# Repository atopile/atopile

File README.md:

# atopile

Design circuit boards with code.

**[Use atopile at atopile.io](https://atopile.io)**

The open-source code in this repository is licensed under [MIT](LICENSE).

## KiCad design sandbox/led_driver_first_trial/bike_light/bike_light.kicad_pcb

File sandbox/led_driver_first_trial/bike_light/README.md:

To add lib components: https://pypi.org/project/easyeda2kicad/

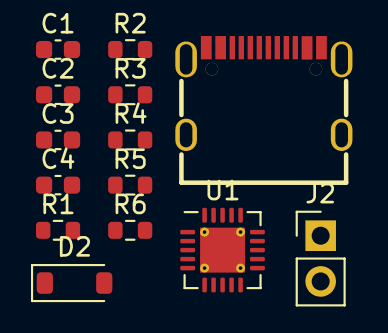
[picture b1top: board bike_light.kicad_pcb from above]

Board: 2 copper layers, 14 parts (0 on the bottom side), 14 nets, no tracks yet.

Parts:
C1: 3.3uF; C_0603_1608Metric
C2: 10uF; C_0603_1608Metric
C3: 33nF; C_0603_1608Metric
C4: 10nF; C_0603_1608Metric
D2: D_SOD-123
J1: USB-C-SMD_KH-TYPE-C-16P
J2: PinHeader_1x02_P2.54mm_Vertical
R1: 6.81k; R_0603_1608Metric
R2: 0.33R; R_0603_1608Metric
R3: 2.4k; R_0603_1608Metric
R4: 100k; R_0603_1608Metric
R5: 1M; R_0603_1608Metric
R6: 75k; R_0603_1608Metric
U1: QFN-20-1EP_4x4mm_P0.5mm_EP2.5x2.5mm_ThermalVias

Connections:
5: R2.2, U1.14
7: C2.1, D2.2, R2.1, R5.1, U1.13
8: J2.1, R4.1
10: R1.1, U1.4
11: C3.1, U1.6
13: R5.2, R6.1, U1.8
14: U1.9, U1.10
15: D2.1, U1.18
27: C4.1, R3.2
34: J1.A6, J1.B6
35: J1.A7, J1.B7
36: J1.A5, J1.B5
37: J1.A8, J1.B8
41: J1.A4, J1.A9, J1.B4, J1.B9

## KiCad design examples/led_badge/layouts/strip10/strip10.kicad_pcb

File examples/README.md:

# Examples

To run examples install faebryk either via pypi or locally with `pip install -e .`
Then you can run them with `python3 examples/<your example>`.

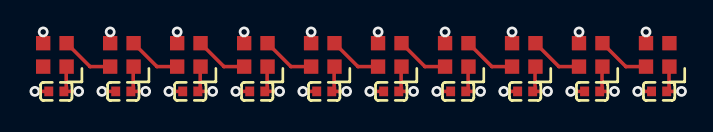
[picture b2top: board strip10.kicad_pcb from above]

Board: 2 copper layers, 20 parts (0 on the bottom side), 11 nets.

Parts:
C1, C2, C3, C4, C5, C6, C7, C8, C9, C10: 100nF; C0402
LED1, LED2, LED3, LED4, LED5, LED6, LED7, LED8, LED9, LED10: LED-SMD_4P-L2.0-W2.0-BR

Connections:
hv: C1.1, C2.1, C3.1, C4.1, C5.1, C6.1, C7.1, C8.1, C9.1, C10.1, LED1.1, LED2.1, LED3.1, LED4.1, LED5.1, LED6.1, LED7.1, LED8.1, LED9.1, LED10.1
leds[1]-data_in-DIN: LED1.2, LED2.4
leds[2]-data_in-DIN: LED2.2, LED3.4
leds[3]-data_in-DIN: LED3.2, LED4.4
leds[4]-data_in-DIN: LED4.2, LED5.4
leds[5]-data_in-DIN: LED5.2, LED6.4
leds[6]-data_in-DIN: LED6.2, LED7.4
leds[7]-data_in-DIN: LED7.2, LED8.4
leds[8]-data_in-DIN: LED8.2, LED9.4
leds[9]-data_in-DIN: LED9.2, LED10.4
lv: C1.2, C2.2, C3.2, C4.2, C5.2, C6.2, C7.2, C8.2, C9.2, C10.2, LED1.3, LED2.3, LED3.3, LED4.3, LED5.3, LED6.3, LED7.3, LED8.3, LED9.3, LED10.3

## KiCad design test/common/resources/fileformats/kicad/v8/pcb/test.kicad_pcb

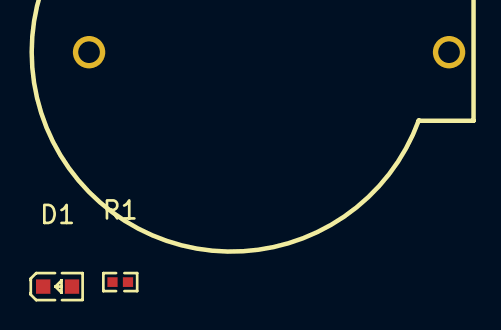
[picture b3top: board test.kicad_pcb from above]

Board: 2 copper layers, 3 parts (0 on the bottom side), 3 nets, no tracks yet.

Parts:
B1: ButtonCell; BAT-TH_BS-02-A1AJ010
D1: LED; LED0603-RD-YELLOW
R1: 40.2Ω; R0402

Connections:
B1-1-R1-2: B1.1, R1.2
B1-2-D1-2: B1.2, D1.2
D1-1-R1-1: D1.1, R1.1

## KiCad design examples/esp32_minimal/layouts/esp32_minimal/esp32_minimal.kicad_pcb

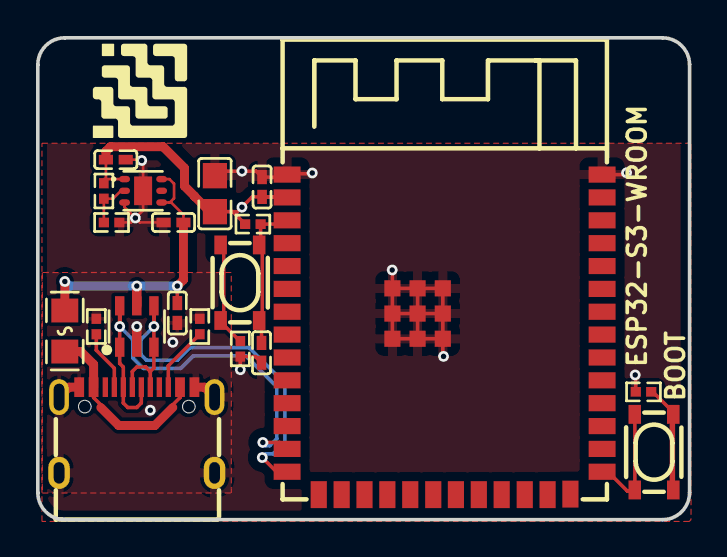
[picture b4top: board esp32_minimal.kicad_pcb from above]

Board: 2 copper layers, 36.2 x 26.8 mm, 20 parts (0 on the bottom side), 13 nets.

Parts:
C1, C2, C10: 1µF ±10% 25V X5R; C0402
C3, C8: 100nF ±10% 16V X7R; C0402
C9: 22µF ±20% 6.3V X5R; C0805
D1: SOT-23-6_L2.9-W1.6-P0.95-LS2.8-BL
F1: F0805
R1, R3: 10kΩ ±1% 62.5mW; R0402
R2, R4: 100Ω ±1% 62.5mW; R0402
R5: 47kΩ ±1% 62.5mW; R0402
R6, R7: 5.1kΩ ±1% 62.5mW; R0402
SW1, SW2: KEY-SMD_4P-L4.2-W3.2-P2.20-LS4.6
U2: WIRELM-SMD_ESP32-S3-WROOM-1
U3: WSON-6_L2.0-W2.0-P0.65-TL-EP
USB1: USB-C-SMD_TYPE-C-6PIN-2MD-073

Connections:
GND: C1.2, C2.2, C3.2, C8.2, C9.2, C10.2, D1.2, R1.2, R2.2, R4.2, R6.2, R7.2, U2.1, U2.40, U2.41, U3.3, U3.7, USB1.1, USB1.12, USB1.13, USB1.14, USB1.15, USB1.16
USB_D_N: D1.1, D1.6, U2.13, USB1.5, USB1.7
USB_D_P: D1.3, D1.4, U2.14, USB1.6, USB1.8
VDIV_OUTPUT: R1.1, R5.2, U3.2
button-input-input-0: R2.1, SW1.1, SW1.2
button-input-input-1: R4.1, SW2.1, SW2.2
cc[0]-line: R6.1, USB1.4
cc[1]-line: R7.1, USB1.10
gpios[0]-output: SW1.3, SW1.4, U2.27
output-output: C10.1, R3.1, SW2.3, SW2.4, U2.3
power-VCC: C2.1, C8.1, C9.1, R3.2, R5.1, U2.2, U3.1
power_in-VCC: C1.1, C3.1, D1.5, F1.2, U3.4, U3.6
power_vbus-VCC: F1.1, USB1.2, USB1.11

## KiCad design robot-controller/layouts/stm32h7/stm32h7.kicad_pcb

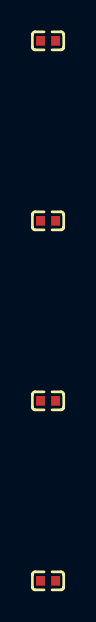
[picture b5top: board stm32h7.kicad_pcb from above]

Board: 2 copper layers, 4 parts (0 on the bottom side), 2 nets, no tracks yet.

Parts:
C1, C2, C3, C4: 0F; C0402

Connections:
hv: C1.1, C2.1, C3.1, C4.1
lv: C1.2, C2.2, C3.2, C4.2

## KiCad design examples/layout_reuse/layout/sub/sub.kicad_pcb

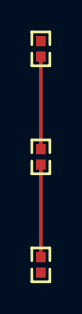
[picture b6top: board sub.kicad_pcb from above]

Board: 2 copper layers, 3 parts (0 on the bottom side), 2 nets.

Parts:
R1, R2, R3: 1kΩ; R0402

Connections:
unnamed[0]-1: R1.2, R2.1
unnamed[0]-2: R2.2, R3.1

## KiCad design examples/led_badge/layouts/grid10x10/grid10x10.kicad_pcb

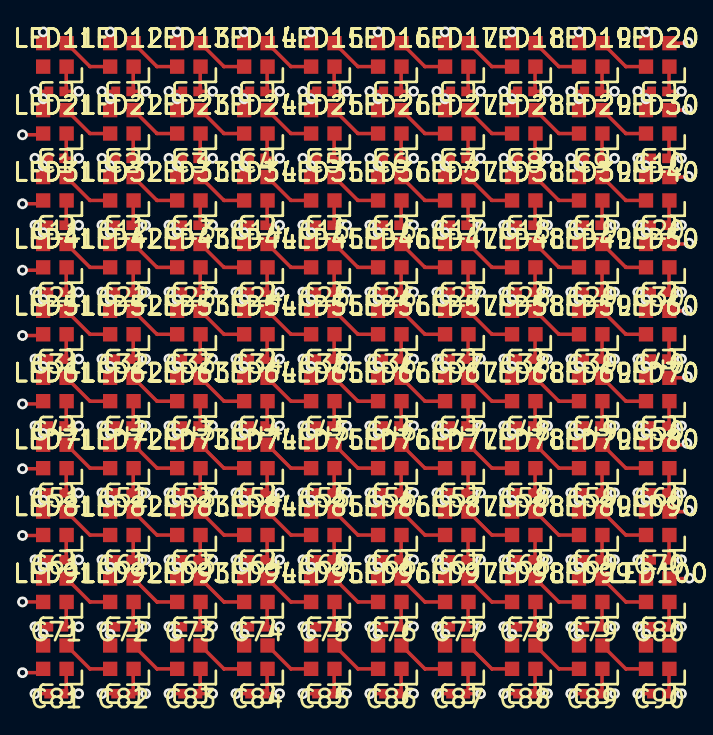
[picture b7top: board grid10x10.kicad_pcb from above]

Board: 4 copper layers, 200 parts (0 on the bottom side), 101 nets.

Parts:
C1, C2, C3, C4, C5, C6, C7, C8, C9, C10, C11, C12, C13, C14, C15, C16, C17, C18, C19, C20, C21, C22, C23, C24, C25, C26, C27, C28, C29, C30, C31, C32, C33, C34, C35, C36, C37, C38, C39, C40, C41, C42, C43, C44, C45, C46, C47, C48, C49, C50, C51, C52, C53, C54, C55, C56, C57, C58, C59, C60, C61, C62, C63, C64, C65, C66, C67, C68, C69, C70, C71, C72, C73, C74, C75, C76, C77, C78, C79, C80, C81, C82, C83, C84, C85, C86, C87, C88, C89, C90, C91, C92, C93, C94, C95, C96, C97, C98, C99, C100: 100nF; C0402
LED1, LED2, LED3, LED4, LED5, LED6, LED7, LED8, LED9, LED10, LED11, LED12, LED13, LED14, LED15, LED16, LED17, LED18, LED19, LED20, LED21, LED22, LED23, LED24, LED25, LED26, LED27, LED28, LED29, LED30, LED31, LED32, LED33, LED34, LED35, LED36, LED37, LED38, LED39, LED40, LED41, LED42, LED43, LED44, LED45, LED46, LED47, LED48, LED49, LED50, LED51, LED52, LED53, LED54, LED55, LED56, LED57, LED58, LED59, LED60, LED61, LED62, LED63, LED64, LED65, LED66, LED67, LED68, LED69, LED70, LED71, LED72, LED73, LED74, LED75, LED76, LED77, LED78, LED79, LED80, LED81, LED82, LED83, LED84, LED85, LED86, LED87, LED88, LED89, LED90, LED91, LED92, LED93, LED94, LED95, LED96, LED97, LED98, LED99, LED100: LED-SMD_4P-L2.0-W2.0-BR

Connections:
DIN: LED1.2, LED2.4
hv: C1.1, C2.1, C3.1, C4.1, C5.1, C6.1, C7.1, C8.1, C9.1, C10.1, C11.1, C12.1, C13.1, C14.1, C15.1, C16.1, C17.1, C18.1, C19.1, C20.1, C21.1, C22.1, C23.1, C24.1, C25.1, C26.1, C27.1, C28.1, C29.1, C30.1, C31.1, C32.1, C33.1, C34.1, C35.1, C36.1, C37.1, C38.1, C39.1, C40.1, C41.1, C42.1, C43.1, C44.1, C45.1, C46.1, C47.1, C48.1, C49.1, C50.1, C51.1, C52.1, C53.1, C54.1, C55.1, C56.1, C57.1, C58.1, C59.1, C60.1, C61.1, C62.1, C63.1, C64.1, C65.1, C66.1, C67.1, C68.1, C69.1, C70.1, C71.1, C72.1, C73.1, C74.1, C75.1, C76.1, C77.1, C78.1, C79.1, C80.1, C81.1, C82.1, C83.1, C84.1, C85.1, C86.1, C87.1, C88.1, C89.1, C90.1, C91.1, C92.1, C93.1, C94.1, C95.1, C96.1, C97.1, C98.1, C99.1, C100.1, LED1.1, LED2.1, LED3.1, LED4.1, LED5.1, LED6.1, LED7.1, LED8.1, LED9.1, LED10.1, LED11.1, LED12.1, LED13.1, LED14.1, LED15.1, LED16.1, LED17.1, LED18.1, LED19.1, LED20.1, LED21.1, LED22.1, LED23.1, LED24.1, LED25.1, LED26.1, LED27.1, LED28.1, LED29.1, LED30.1, LED31.1, LED32.1, LED33.1, LED34.1, LED35.1, LED36.1, LED37.1, LED38.1, LED39.1, LED40.1, LED41.1, LED42.1, LED43.1, LED44.1, LED45.1, LED46.1, LED47.1, LED48.1, LED49.1, LED50.1, LED51.1, LED52.1, LED53.1, LED54.1, LED55.1, LED56.1, LED57.1, LED58.1, LED59.1, LED60.1, LED61.1, LED62.1, LED63.1, LED64.1, LED65.1, LED66.1, LED67.1, LED68.1, LED69.1, LED70.1, LED71.1, LED72.1, LED73.1, LED74.1, LED75.1, LED76.1, LED77.1, LED78.1, LED79.1, LED80.1, LED81.1, LED82.1, LED83.1, LED84.1, LED85.1, LED86.1, LED87.1, LED88.1, LED89.1, LED90.1, LED91.1, LED92.1, LED93.1, LED94.1, LED95.1, LED96.1, LED97.1, LED98.1, LED99.1, LED100.1
leds[1]-data_in-DIN: LED11.2, LED12.4
leds[1]-data_in-DIN-1: LED21.2, LED22.4
leds[1]-data_in-DIN-2: LED31.2, LED32.4
leds[1]-data_in-DIN-3: LED41.2, LED42.4
leds[1]-data_in-DIN-4: LED51.2, LED52.4
leds[1]-data_in-DIN-5: LED61.2, LED62.4
leds[1]-data_in-DIN-6: LED71.2, LED72.4
leds[1]-data_in-DIN-7: LED81.2, LED82.4
leds[1]-data_in-DIN-8: LED91.2, LED92.4
leds[2]-data_in-DIN: LED2.2, LED3.4
leds[2]-data_in-DIN-1: LED12.2, LED13.4
leds[2]-data_in-DIN-2: LED22.2, LED23.4
leds[2]-data_in-DIN-3: LED32.2, LED33.4
leds[2]-data_in-DIN-4: LED42.2, LED43.4
leds[2]-data_in-DIN-5: LED52.2, LED53.4
leds[2]-data_in-DIN-6: LED62.2, LED63.4
leds[2]-data_in-DIN-7: LED72.2, LED73.4
leds[2]-data_in-DIN-8: LED82.2, LED83.4
leds[2]-data_in-DIN-9: LED92.2, LED93.4
leds[3]-data_in-DIN: LED3.2, LED4.4
leds[3]-data_in-DIN-1: LED13.2, LED14.4
leds[3]-data_in-DIN-2: LED23.2, LED24.4
leds[3]-data_in-DIN-3: LED33.2, LED34.4
leds[3]-data_in-DIN-4: LED43.2, LED44.4
leds[3]-data_in-DIN-5: LED53.2, LED54.4
leds[3]-data_in-DIN-6: LED63.2, LED64.4
leds[3]-data_in-DIN-7: LED73.2, LED74.4
leds[3]-data_in-DIN-8: LED83.2, LED84.4
leds[3]-data_in-DIN-9: LED93.2, LED94.4
leds[4]-data_in-DIN: LED4.2, LED5.4
leds[4]-data_in-DIN-1: LED14.2, LED15.4
leds[4]-data_in-DIN-2: LED24.2, LED25.4
leds[4]-data_in-DIN-3: LED34.2, LED35.4
leds[4]-data_in-DIN-4: LED44.2, LED45.4
leds[4]-data_in-DIN-5: LED54.2, LED55.4
leds[4]-data_in-DIN-6: LED64.2, LED65.4
leds[4]-data_in-DIN-7: LED74.2, LED75.4
leds[4]-data_in-DIN-8: LED84.2, LED85.4
leds[4]-data_in-DIN-9: LED94.2, LED95.4
leds[5]-data_in-DIN: LED5.2, LED6.4
leds[5]-data_in-DIN-1: LED15.2, LED16.4
leds[5]-data_in-DIN-2: LED25.2, LED26.4
leds[5]-data_in-DIN-3: LED35.2, LED36.4
leds[5]-data_in-DIN-4: LED45.2, LED46.4
leds[5]-data_in-DIN-5: LED55.2, LED56.4
leds[5]-data_in-DIN-6: LED65.2, LED66.4
leds[5]-data_in-DIN-7: LED75.2, LED76.4
leds[5]-data_in-DIN-8: LED85.2, LED86.4
leds[5]-data_in-DIN-9: LED95.2, LED96.4
leds[6]-data_in-DIN: LED6.2, LED7.4
leds[6]-data_in-DIN-1: LED16.2, LED17.4
leds[6]-data_in-DIN-2: LED26.2, LED27.4
leds[6]-data_in-DIN-3: LED36.2, LED37.4
leds[6]-data_in-DIN-4: LED46.2, LED47.4
leds[6]-data_in-DIN-5: LED56.2, LED57.4
leds[6]-data_in-DIN-6: LED66.2, LED67.4
leds[6]-data_in-DIN-7: LED76.2, LED77.4
leds[6]-data_in-DIN-8: LED86.2, LED87.4
leds[6]-data_in-DIN-9: LED96.2, LED97.4
leds[7]-data_in-DIN: LED7.2, LED8.4
leds[7]-data_in-DIN-1: LED17.2, LED18.4
leds[7]-data_in-DIN-2: LED27.2, LED28.4
leds[7]-data_in-DIN-3: LED37.2, LED38.4
leds[7]-data_in-DIN-4: LED47.2, LED48.4
leds[7]-data_in-DIN-5: LED57.2, LED58.4
leds[7]-data_in-DIN-6: LED67.2, LED68.4
leds[7]-data_in-DIN-7: LED77.2, LED78.4
leds[7]-data_in-DIN-8: LED87.2, LED88.4
leds[7]-data_in-DIN-9: LED97.2, LED98.4
leds[8]-data_in-DIN: LED8.2, LED9.4
leds[8]-data_in-DIN-1: LED18.2, LED19.4
leds[8]-data_in-DIN-2: LED28.2, LED29.4
leds[8]-data_in-DIN-3: LED38.2, LED39.4
leds[8]-data_in-DIN-4: LED48.2, LED49.4
leds[8]-data_in-DIN-5: LED58.2, LED59.4
leds[8]-data_in-DIN-6: LED68.2, LED69.4
leds[8]-data_in-DIN-7: LED78.2, LED79.4
leds[8]-data_in-DIN-8: LED88.2, LED89.4
leds[8]-data_in-DIN-9: LED98.2, LED99.4
leds[9]-data_in-DIN: LED9.2, LED10.4
leds[9]-data_in-DIN-1: LED19.2, LED20.4
leds[9]-data_in-DIN-2: LED29.2, LED30.4
leds[9]-data_in-DIN-3: LED39.2, LED40.4
leds[9]-data_in-DIN-4: LED49.2, LED50.4
leds[9]-data_in-DIN-5: LED59.2, LED60.4
leds[9]-data_in-DIN-6: LED69.2, LED70.4
leds[9]-data_in-DIN-7: LED79.2, LED80.4
leds[9]-data_in-DIN-8: LED89.2, LED90.4
leds[9]-data_in-DIN-9: LED99.2, LED100.4
lv: C1.2, C2.2, C3.2, C4.2, C5.2, C6.2, C7.2, C8.2, C9.2, C10.2, C11.2, C12.2, C13.2, C14.2, C15.2, C16.2, C17.2, C18.2, C19.2, C20.2, C21.2, C22.2, C23.2, C24.2, C25.2, C26.2, C27.2, C28.2, C29.2, C30.2, C31.2, C32.2, C33.2, C34.2, C35.2, C36.2, C37.2, C38.2, C39.2, C40.2, C41.2, C42.2, C43.2, C44.2, C45.2, C46.2, C47.2, C48.2, C49.2, C50.2, C51.2, C52.2, C53.2, C54.2, C55.2, C56.2, C57.2, C58.2, C59.2, C60.2, C61.2, C62.2, C63.2, C64.2, C65.2, C66.2, C67.2, C68.2, C69.2, C70.2, C71.2, C72.2, C73.2, C74.2, C75.2, C76.2, C77.2, C78.2, C79.2, C80.2, C81.2, C82.2, C83.2, C84.2, C85.2, C86.2, C87.2, C88.2, C89.2, C90.2, C91.2, C92.2, C93.2, C94.2, C95.2, C96.2, C97.2, C98.2, C99.2, C100.2, LED1.3, LED2.3, LED3.3, LED4.3, LED5.3, LED6.3, LED7.3, LED8.3, LED9.3, LED10.3, LED11.3, LED12.3, LED13.3, LED14.3, LED15.3, LED16.3, LED17.3, LED18.3, LED19.3, LED20.3, LED21.3, LED22.3, LED23.3, LED24.3, LED25.3, LED26.3, LED27.3, LED28.3, LED29.3, LED30.3, LED31.3, LED32.3, LED33.3, LED34.3, LED35.3, LED36.3, LED37.3, LED38.3, LED39.3, LED40.3, LED41.3, LED42.3, LED43.3, LED44.3, LED45.3, LED46.3, LED47.3, LED48.3, LED49.3, LED50.3, LED51.3, LED52.3, LED53.3, LED54.3, LED55.3, LED56.3, LED57.3, LED58.3, LED59.3, LED60.3, LED61.3, LED62.3, LED63.3, LED64.3, LED65.3, LED66.3, LED67.3, LED68.3, LED69.3, LED70.3, LED71.3, LED72.3, LED73.3, LED74.3, LED75.3, LED76.3, LED77.3, LED78.3, LED79.3, LED80.3, LED81.3, LED82.3, LED83.3, LED84.3, LED85.3, LED86.3, LED87.3, LED88.3, LED89.3, LED90.3, LED91.3, LED92.3, LED93.3, LED94.3, LED95.3, LED96.3, LED97.3, LED98.3, LED99.3, LED100.3
rows[1]-data_in-line: LED10.2, LED11.4
rows[2]-data_in-line: LED20.2, LED21.4
rows[3]-data_in-line: LED30.2, LED31.4
rows[4]-data_in-line: LED40.2, LED41.4
rows[5]-data_in-line: LED50.2, LED51.4
rows[6]-data_in-line: LED60.2, LED61.4
rows[7]-data_in-line: LED70.2, LED71.4
rows[8]-data_in-line: LED80.2, LED81.4
rows[9]-data_in-line: LED90.2, LED91.4

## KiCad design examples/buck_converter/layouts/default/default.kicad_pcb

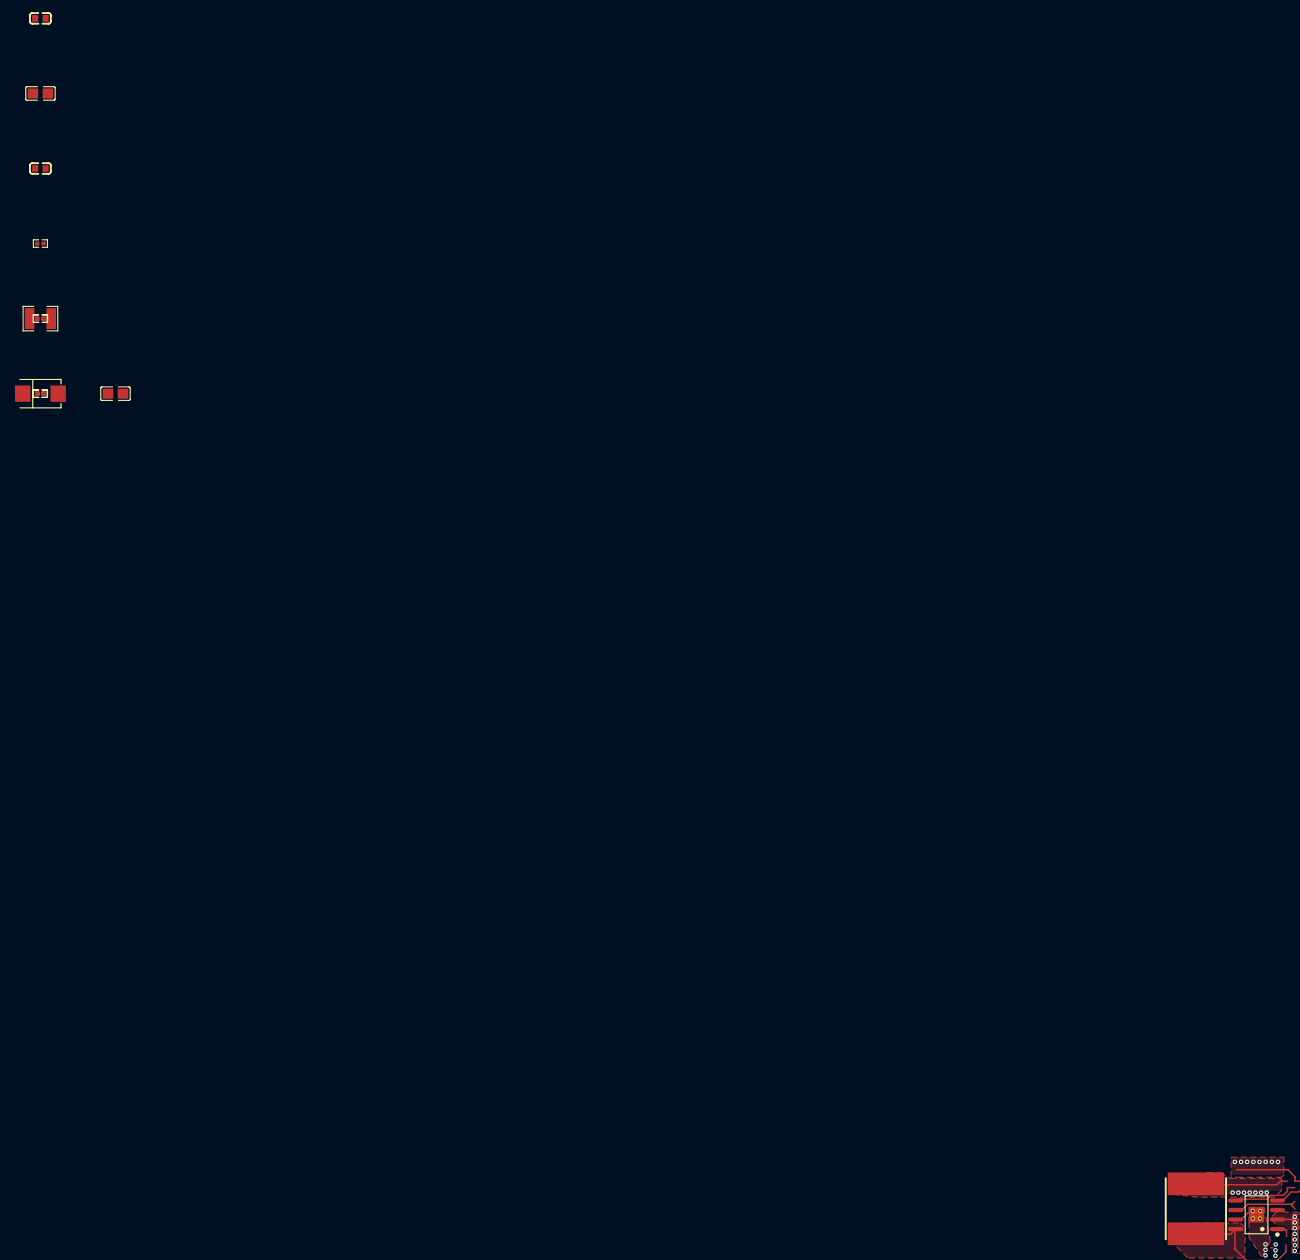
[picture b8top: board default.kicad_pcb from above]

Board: 2 copper layers, 14 parts (0 on the bottom side), 10 nets.

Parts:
C1, C4: 0F; C0805
C2, C3: 0F; C0603
D1: SMB_L4.6-W3.6-LS5.3-RD
L1: L 0H; IND-SMD_L8.0-W8.0
R1: 10200Ω; R0402
R2: 53600Ω; R0402
R3: 16900Ω; R0402
R4: 240000Ω; R0402
R5: 450000Ω; R0402
R6: 10000Ω; R1210
R7: 91000Ω; R0402
U1: SOIC-8_L5.0-W4.0-P1.27-LS6.0-BL-EP2.0

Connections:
EN: R5.2, R7.1, U1.3
FB: R1.1, R2.2, U1.5
RT_CLK: R4.1, U1.4
anode: C1.2, C3.2, C4.2, D1.2, R1.2, R4.2, R6.2, R7.2, U1.7, U1.9
c_comp1-power-hv: C3.1, R3.1, U1.6
c_comp-power-hv: C4.1, R3.2
c_in-power-hv: C1.1, R5.1, U1.2
capacitors[3]-power-hv: L1.2, R2.1, R6.1
cathode: C2.2, D1.1, L1.1, U1.8
hv: C2.1, U1.1

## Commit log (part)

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2026-03-03 fix extra info loading
2026-03-03 change button name BOM -> iBom
2026-03-03 UI: fix button icon+txt width cutoff side panel
2026-03-03 match kicad rotation convention
2026-03-03 Ghostless drag cache and add frontend closed-loop regression
2026-03-03 playground: spinner terminal lines and nolaunch flag
2026-03-03 Show status-bar spinner while execute-action requests are pending
2026-03-03 layout-server: remove notify-selection and add timestamped standalone logs
2026-03-03 web-ide: gate layout auto-open on render-model readiness
2026-03-04 cleanup layout server action flow and remove dead code
2026-03-04 set from info to warning
2026-03-04 downgrade infos to debugs during build
2026-03-04 UI: Fast layout viewer (#1758)
    Make fast enough to make working with hyperion (10k footprints)
    possible.
    <!-- CURSOR_SUMMARY -->
    ---
    > [!NOTE]
    > <sup>[Cursor Bugbot](https://cursor.com/dashboard?tab=bugbot) is
2026-03-04 mixed estimation wip
2026-03-04 web-ide: use mainline layout editor webview template
2026-03-04 cleanup code
2026-03-04 fix broken imports and type graph for library tool. fixes #1734
2026-03-04 Remove comments for API and user literal behavior
    Removed comments indicating expected behavior for API and user literals.
2026-03-04 MCP: Fix broken imports and type graph for library tool (#1763)
    <!--
    Ensure PR title follows the correct format:
    - Scope prefix first (capitalized)
    - Colon separator
    - Action verb (Fix, Add, Update, Move, etc.)
    - Clear description of what changed
2026-03-04 color modes
2026-03-04 update docstring on fabll_minimal
2026-03-04 fix layout re-use example
2026-03-04 checkin work
2026-03-04 Address review comments: clean up architecture and BOM endpoint
    - Remove duplicated /api/layout/bom endpoint from layout_server (use
    existing /api/bom from routes/artifacts.py instead)
    - Return project_root/target_name in openInteractiveBom action response
    instead of emitting a separate WS event
    - Remove OPEN_INTERACTIVE_BOM event type from backend and frontend
    - Sidebar handles iBOM open signal directly from action response
2026-03-04 rewrite playground as python service with typed config and infra cli
2026-03-04 increase max to 20
2026-03-04 combine the picking examples
2026-03-04 restructure files
2026-03-05 more vdiv equations
2026-03-05 move to backend
2026-03-05 fix relevance filtering wip
2026-03-05 Make Editor container required, remove global DOM fallback
    The text overlay canvas now always positions relative to a container
    element instead of falling back to document.body with fixed positioning, removing the assumption that the editor owns the entire page.
2026-03-05 Expressions: support expression conditions in Mapping.MakeChild
2026-03-05 Examples: update examples (#1769)
    - simpler I2C example
    - fix led badge builds
2026-03-05 fix group selection single and double click in iBOM
2026-03-05 hide textoverlay items when in readonly-mode
2026-03-05 Fix web-ide backend reuse and remove debug residue
2026-03-05 Commit remaining web IDE changes
2026-03-05 Docs: point PR instructions to template
2026-03-05 Remove voltage divider end-to-end test
2026-03-05 Refactor end-to-end PCB test helpers
2026-03-05 test: refactor end-to-end PCB test helpers (#1772)
    ## Summary
    - move shared PCB inspection helpers into `test/end_to_end/utils.py`
    - make all end-to-end tests preserve their temp workspace on failure via
    an autouse fixture
    - normalize the remaining end-to-end tests to `tmp_path`
    ## Testing
2026-03-05 Refactor webview wrappers and bridge runtime
2026-03-05 Always run demo mode in web IDE
2026-03-05 UI: separate JLCPCB setup fees from unit costs (#1774)
    Currently all components get the JLC setup fee added to them, so a
    resistor will cost $3.001, but the fee is added to EACH part, so 5x
    resistors cost $15.005.
    This splits out the setup fee and displays it separately in the BOM.
2026-03-05 CI: Update regression workflow triggers and runner path
2026-03-05 Test: Remove gh dependency from regression clones
2026-03-05 Add install-as-package flow and subproject build selection
2026-03-05 Test: Provision packages repo consistently in regression CI
2026-03-05 unify trait patern
2026-03-05 Library: Add Multi State Functionality to Addressor (#1775)
    ti-ina228 uses 4 address pins, each of which can have 4 states by being
    tied to a different rail. This can be generalized to an addressor that
    takes n address lines and connects them to m states.
    Generalized the behavior of the std lib Addressor to incorporate the
    multistate design. Old functionality was just a multi pin 2 state/binary
    addressor (m=2 case), which is a subset of the new functionality which
2026-03-05 Polish part package scaffolding and build queue
2026-03-05 Improve regression test reporting and reduce CI concurrency
2026-03-05 Fix agent turn resumption and mention UX
2026-03-05 Build: Fix TestPyPI deploy versioning
2026-03-06 Fix missing identifier in local file dependencies
    (cherry picked from commit 53c0e09ddbecbfd2eabd626507ab174ddb3106b3)
2026-03-06 Fix missing identifier in local file dependencies
2026-03-06 Fix local package dist generation without repository
2026-03-06 Tune demo 3D board rendering
2026-03-06 Apply pre-commit formatting fixes
2026-03-06 Fix demo layout target and proxy websocket dispatch
2026-03-06 Fix agent route compatibility exports
2026-03-06 Improve agent progress summaries and package guidance
2026-03-06 Keep agent checklist state across turns
2026-03-06 Tighten agent interface guidance and fix tool trace UI
2026-03-06 Move sidebar file watching into backend
2026-03-06 refactor: colorize demo scene glow with brand orange
2026-03-06 Add graceful stop and interrupt flow
2026-03-06 Polish agent question and session UI
2026-03-06 Refresh generated agent progress schema
2026-03-06 Honor latest guidance on agent stop handoff
2026-03-06 Make agent tool history scrollable
2026-03-06 fail build early with multiple pcb or multiple stackup per pcb
2026-03-06 fix no board definition check
2026-03-06 implementing feedback
2026-03-06 Core: Refactor logging implementation, allow audience field (#1689)
    - refactor callsites to use of AtoLogger everywhere
    - audience field actually useable
    - refactor clear distinction between ConsoleLogHandler and DBLogHandler
    - logs not associated with a build or test still get saved to DB
    (unscoped logger)
    - remove silent passes for log failures
2026-03-06 add layout and 3d viewer files from main
2026-03-06 Fix checklist tool ID contract
2026-03-06 Improve agent support for nested package work
2026-03-06 Transformer: Expose standardize designators option
2026-03-06 Expand stdlib interface allowlist
2026-03-06 Transformer: Deduplicate designators in PCB layout
2026-03-06 Consolidate file watching in backend
2026-03-06 fix circular import error in CI
2026-03-06 Trim unrelated workflow and UI polish changes
2026-03-06 Remove experimental CLI chat client
2026-03-06 Revert merged gentypegraph change
2026-03-06 debug log connected
2026-03-06 Revert websocket action refactor
2026-03-06 Revert stdlib-related changes
2026-03-06 Remove agent autolayout tools
2026-03-06 Relocate agent tests alongside source modules
2026-03-06 Relocate projects domain test ליד source module
2026-03-06 Revert package and library spillover
2026-03-06 Remove legacy agent orchestrator
2026-03-06 properly handle escape characters in kicad
2026-03-07 group bus logging
2026-03-07 cache units
2026-03-07 new arch
2026-03-07 remove frontend skills
2026-03-07 fast pad match (12s -> 300ms). didnt read too deeply
    Summary
    Problem: The "Loading PCB" build stage took ~12s for the quickstart example.
    Root cause: Repeated graph traversals via extract_singleton() on pad name/number properties. For a 144-pad component:
    - find_matching_pad was called 144 times, each time sorting 144 pads by pad_name (triggering ~1000 extract_singleton() calls
    per sort)
    - bind_footprint iterated all pads comparing fpad.pad_name/fpad.pad_number against PCB pads using FuncSet (O(n²) with graph
2026-03-07 Fix agent run turn invocation
2026-03-07 Polish agent build and tool panels
2026-03-07 Remove package worker agent orchestration
2026-03-07 Fix agent interrupt response and summary model default
2026-03-07 dont send domain default to picker api
2026-03-07 rpc wip
2026-03-07 fix script
2026-03-08 fix bug
2026-03-09 add testcase to test file
2026-03-09 KiCad: Fix S-expression string escape handling (#1789)
    ## Description
    Fix `_unescape_string` and `writeEscapedString` in the Zig S-expression
    engine to properly handle backslash escape sequences (`\\n`, `\\r`,
    `\\\\`, `\\"`).
    Previously, `_unescape_string` stripped all backslashes
    indiscriminately, turning `\\n` into `n`. And `writeEscapedString` only
2026-03-09 atopile: Use ConfigFlag() for ato env variables
2026-03-09 refresh parity plan
2026-03-09 sublinear scaling
2026-03-09 add detailed sidebar views for parts, packages, and migrate
2026-03-09 Simplify chat feature gating
2026-03-09 Consolidate agent dataclasses
2026-03-09 Trim agent implementation config knobs
2026-03-09 Avoid zig build lock timeout on parallel startup
2026-03-09 Allow agent to create yaml files
2026-03-09 Clarify package-by-package build workflow
2026-03-09 refactor: move demo code into board_demo
2026-03-09 refactor: batch demo glb optimization
2026-03-09 Remove vite chat flag fallback
2026-03-09 refactor: use gltfpack for demo glb optimization
2026-03-09 fast without cacheing
2026-03-09 UI: Apply VS Code theme styling to layout viewer (#1793)
    <img width="2077" height="1517" alt="Screenshot 2026-03-09 at 2 31
    45 PM"
    src="https://github.com/user-attachments/assets/bedfe3af-a31a-4b72-9ac8-148028e53532"
    />
    <img width="2077" height="1517" alt="Screenshot 2026-03-09 at 2 31
    13 PM"
2026-03-09 add back old project/targe selector, refactor websockets/actions and some file locations
2026-03-09 use camelmodel everywhere
2026-03-09 orange glow
2026-03-10 logo cone
2026-03-10 camera default rotate
2026-03-10 localize retyped path
2026-03-10 revert node to main, fix all .is_unit references on unit instances
2026-03-10 bug fix
2026-03-10 import statements in detail view
2026-03-10 update led badge comment
2026-03-10 file tree edit
2026-03-10 ISO3166 add full names
2026-03-10 UI: Add PCB stackup viewer
2026-03-10 revert esp32minimal changes to main
2026-03-10 Add bus traits to busses in standard library
2026-03-10 allow str from ato code
2026-03-10 LIBRARY: Add bus spec and role traits
2026-03-10 update node count test
2026-03-10 Rename to DataBus, shorten trait names
2026-03-10 add (already) missing import in i2c example, add immutable trait to has_databus_role
2026-03-10 Fix CAN multicontroller flag
2026-03-10 Add bus_traits example
2026-03-10 Refactor bus_checks to share discovery logic and add source locations
2026-03-10 switch to lazy registration of unit types in typegraph
2026-03-10 fix test expectations
2026-03-10 replace dimensionless with none
2026-03-10 reset test file
2026-03-10 Packages: Improve error messages, retries, and progress UX
2026-03-11 copy definition node pointer in _clone_type
2026-03-11 find layout of og type, group by definition block, copy layout path to clones
2026-03-11 add triple retype test
2026-03-11 log wip
2026-03-11 Two-pass resolution, parallel downloads, per stage logging
2026-03-11 convert Makechild to use concrete type and move test
2026-03-11 fix lost logs and missing @
2026-03-11 prek formatting
2026-03-11 fix pytest
2026-03-11 priomitives are back in preview
2026-03-11 junk we seem to need
2026-03-11 Center rectangular board shape origin
2026-03-11 Integrate board shape into footprint lifecycle
2026-03-11 switch to fileformat test
2026-03-11 Fix duplicate footprint association setup
2026-03-12 Squashed commit of the following:
    commit e8630c94f32d3c8c0528a4335cac510ccb43343e
    Author: Ray Allen <ray@atopile.io>
    Date: Wed Mar 11 16:04:51 2026 -0700
    fix 3d viewer
    commit 2587e9bbdda0010a47bea1733d7ea75a8518f644
    Merge: 25cb22b2 752c2d62
2026-03-12 uncertainty estimation wip
2026-03-12 working baseline 2
2026-03-12 working baseline
2026-03-12 reduce diff
2026-03-12 more refactor
2026-03-12 cleanup
2026-03-13 pre-sized batch alloc
2026-04-02 Fix typo in CLAUDE.md
    correspondig > corresponding
2026-04-02 Update pyproject.toml
    Pin `more-itertools` dependency to less than version 11
